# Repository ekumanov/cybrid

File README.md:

# Cybrid

**A DIY hybrid piano: a real grand piano action turned into a MIDI controller.**

Instruments with a real wooden piano action and a digital sound engine are called *hybrid* pianos;
the Yamaha AvantGrand N1X I own is one. I wondered whether I could build something similar myself,
and in 2020 finished **Cybrid**: one optical sensor above each hammer of a grand piano action
measures the hammer's speed just before it hits the stop rail, and a Teensy turns that into MIDI.
The name was suggested on a piano forum: **Cyb**erGene (my nickname) + hy**brid**.

I'm a Java engineer and had no experience with electronics, PCB design, microcontrollers or piano
regulation when I started, so I learned it all along the way. V1 is the result: it works and I
play it daily, but many decisions are clumsy. This repository documents it as built, and is
structured so that better versions can follow.

▶ **Demo video:**

## How it works, in short

- A **CNY70** reflective optical sensor above each hammer shank gives a voltage that rises as the
  hammer approaches.
- Three **LM339** comparators per key turn it into three digital signals: the hammer is past the
  damper point, the escapement point, or the strike point. Trimpots set the three points.
- A **Teensy** scans all 88 keys in a few microseconds through a shared bus, times the flight from
  escapement to strike, and sends MIDI note-on with a velocity derived from it.

Full explanation: [How it works](docs/v1/how-it-works.md).

<table>
<tr>
<td align="center"><br><b>Sensor board</b> × 88</td>
<td align="center"><br><b>Note board</b> × 18 (5 keys each)</td>
<td align="center"><br><b>Teensy board</b> × 1</td>
</tr>
</table>

## Versions

| Version | Status | |
|---|---|---|
| **V1** | Built 2019–2020, played daily. Comparators + trimpots, Teensy 3.6/4.1, hand-made ribbon cable. | [hardware](hardware/v1) · [firmware](firmware/v1) · [docs](docs/v1) |

## Documentation

| | |
|---|---|
| [How it works](docs/v1/how-it-works.md) | Sensing principle, grouping and multiplexing, scanning algorithm, velocity |
| [Hardware](hardware/v1/README.md) | The three boards: schematics, 3D renders, bill of materials, manufacturing files |
| [Build guide](docs/v1/build-guide.md) | Soldering, mounting, wiring, power, the ribbon cable, known problems |
| [Firmware](firmware/v1/README.md) | Building and flashing (Arduino IDE or PlatformIO), configuration, tests |
| [Calibration](docs/v1/calibration.md) | Setting the three points of every key |
| [Photo gallery](docs/v1/gallery.md) | The V1 build in pictures |
| [Changelog](CHANGELOG.md) | |

## Repository layout

```
cybrid/
├── hardware/v1/      KiCad 10 projects for the three boards, export script for fab outputs
├── firmware/v1/      Teensy firmware (PlatformIO project), calibration sketches, host tests
├── docs/
│   ├── v1/           how it works, build guide, calibration, gallery
│   └── images/v1/    photos and board renders
├── LICENSES/         full license texts
└── .github/          CI: firmware build + tests, hardware export
```

Each future version gets its own `hardware/vN`, `firmware/vN` and `docs/vN`, so V1 stays buildable
as it is.

## Community

Discussion thread on the
[PianoClack forum](https://pianoclack.com/forum/d/107-cybrid-a-diy-midi-controller-with-grand-piano-action).
I'm glad Cybrid has inspired other projects, several of them better designed and easier to
reproduce. Questions, issues and pull requests are welcome.

## Credits

Using voltage comparators to turn the analog sensor signal into fast digital signals was
suggested by **Marcos Daniel** on the PianoWorld forums. Everything else (multiplexing, PCB design,
firmware and the integration with the grand piano action) is by Evgeni Kumanov (CyberGene).

## License

Open source hardware and software. Hardware is under
[CERN-OHL-P-2.0](LICENSES/CERN-OHL-P-2.0.txt), software under [MIT](LICENSES/MIT.txt), and
documentation and photos under [CC-BY-4.0](LICENSES/CC-BY-4.0.txt). See [LICENSE](LICENSE) for
details.

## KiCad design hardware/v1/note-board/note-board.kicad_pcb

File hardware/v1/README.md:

# Cybrid V1 hardware

KiCad sources for the three V1 boards, as fabricated and built in 2019–2020. How they work together is
explained in [How it works](../../docs/v1/how-it-works.md); assembly is in the
[build guide](../../docs/v1/build-guide.md).

| | Sensor board | Note board | Teensy board |
|---|---|---|---|
| 3D render |  |  |  |
| As built |  |  |  |
| Role | 1 CNY70 above one hammer shank | 5 keys: comparators, trimpots, bus transceivers | Teensy, ribbon-cable socket, power distribution |
| Qty for 88 keys | 88 | 18 | 1 |
| Size | 24.1 × 8.9 mm | 53.3 × 76.2 mm | 57.1 × 87.6 mm |
| Layers | 2 | 2 | 2 |
| Schematic | [PDF](sensor-board/sensor-board-schematic.pdf) | [PDF](note-board/note-board-schematic.pdf) | [PDF](teensy-board/teensy-board-schematic.pdf) |
| KiCad project | [`sensor-board/`](sensor-board) | [`note-board/`](note-board) | [`teensy-board/`](teensy-board) |

Top and bottom renders of every board are in [`docs/images/v1/boards`](../../docs/images/v1/boards).
The 3D renders show no Teensy and no USB-B socket, because KiCad's library has no 3D models for them.

## Opening the designs

Install [KiCad](https://www.kicad.org/download/) **10 or newer** and open a board's `.kicad_pro`
file. No extra libraries are needed: the schematic symbols and footprints are embedded in the
design files, and the 3D models come from KiCad's standard library.

```
hardware/v1/
├── export.sh                 regenerates all outputs (see below)
├── tools/                    one-off scripts used to modernise the 2020 files (kept for reference)
├── sensor-board/
│   ├── sensor-board.kicad_pro    project
│   ├── sensor-board.kicad_sch    schematic
│   ├── sensor-board.kicad_pcb    board
│   └── sensor-board-schematic.pdf
├── note-board/   (same layout)
└── teensy-board/ (same layout)
```

## Manufacturing

Generate the fabrication files with:

```bash
hardware/v1/export.sh
```

This writes `hardware/v1/build/<board>/` (not committed): Gerbers and Excellon drill files in
`fab/` and zipped as `<board>-fab.zip` (upload that to any PCB fab), the schematic PDF, the BOM as
CSV, 3D renders, and ERC/DRC reports. `DOCS=1 hardware/v1/export.sh` also refreshes the schematic
PDFs and renders committed for the docs. GitHub Actions runs the same export on every change to
`hardware/` and keeps the outputs as a downloadable artifact.

My boards were made as standard 2-layer, 1.6 mm FR-4 boards with **white solder mask and black
silkscreen**. All SMD parts are 0603 or SOIC, hand-solderable.

## Bill of materials

Per board, from the schematics (`<board>-bom.csv` from the export has the reference designators).
The links are where I bought parts in 2020 (a Bulgarian distributor); any equivalent part works.

### Note board (× 18 for 88 keys)

| Qty | Part | Value / type | Package | Refs |
|---|---|---|---|---|
| 4 | Quad voltage comparator | LM339AD (TI) | SOIC-14 | CMP1–CMP4 |
| 2 | Octal bus transceiver, 3-state | SN74LVC245ADWR (TI) | SOIC-20 wide (7.5 mm) | TX1, TX2 |
| 15 | Trimpot, multi-turn, top adjust | 10 kΩ (20 kΩ also works), Bourns 3296W | THT | RV11–RV53 |
| 17 | Resistor | 10 kΩ | 0603 | R1, R11–R44 |
| 5 | Resistor (sensor load) | 4.7 kΩ | 0603 | R18, R28, R38, R48, R58 |
| 6 | Capacitor, ceramic (back side) | 100 nF | 0603 | C1–C6 |
| 1 | Box header, straight | 2×17, 2.54 mm (IDC-34) | THT | COMM1 |
| 2 | Pin header + 1 jumper | 2×9, 2.54 mm | THT | SEL1, SEL2 |
| 5 | Pin header (back side, sensor cables) | 1×3, 2.54 mm | THT | J1–J5 |
| 2 | Wire-to-board header, power in/out | JST XH 3-pin (B3B-XH-A) | THT | PWR1, PWR2 |

### Sensor board (× 88)

| Qty | Part | Value / type | Package | Refs |
|---|---|---|---|---|
| 1 | Reflective optical sensor | Vishay CNY70 | THT | S1 |
| 1 | Resistor (LED current, ~16 mA) | 240 Ω | 0603 | R1 |
| 1 | Pin header, right angle, male (cut from a longer strip) | 1×3, 2.54 mm | THT | J1 |

### Teensy board (× 1)

| Qty | Part | Value / type | Package | Refs |
|---|---|---|---|---|
| 1 | Microcontroller | Teensy 4.1 (or 3.6), with pin headers | module | CTL1 |
| 1 | Box header, straight | 2×17, 2.54 mm (IDC-34) | THT | COMM1 |
| 4 | Wire-to-board header, power out | JST XH 3-pin (B3B-XH-A) | THT | PWR1–PWR4 |
| 1 | USB-B socket (power input only) | | THT | USB1 |
| 1 | DC barrel jack (alternative power input) | | THT | J11 |
| 1 | Pin header + jumper (3.3 V from Teensy, not recommended) | 1×2, 2.54 mm | THT | JP1 |
| 3 | Resistor, pedal current limit | **not fitted** | 0603 | R1–R3 |
| 1 | 3.3 V linear regulator, on a small perfboard (not on the PCB) | any, low current | | |

### Cabling and mechanics

| Qty (88 keys) | Part |
|---|---|
| 88 | 3-wire female–female Dupont cable, 10 cm (sensor to note board) |
| 19 | IDC-34 ribbon connector (18 note boards + Teensy board) |
| ~1.5 m | 34-wire ribbon cable, 1.27 mm pitch |
| 2 per board | JST XH 3-pin housings + crimp contacts, and solid-core wire for the power chain |
| 1 | 5 V power supply, ≥ 2 A (USB charger) |
| 1 | Aluminium profile for the sensor rail, threaded rods and nuts to fix it to the action |

### Totals for 88 keys

| Part | Qty |
|---|---|
| CNY70 | 88 |
| LM339AD | 72 |
| SN74LVC245ADWR | 36 |
| Trimpot 10 kΩ, Bourns 3296W | 270 (264 used) |
| Resistor 0603: 10 kΩ / 4.7 kΩ / 240 Ω | 306 / 90 / 88 |
| Capacitor 0603 100 nF | 108 |

## What changed in 2026

The boards were drawn in KiCad 5.0 in 2019–2020. In 2026 the projects were migrated to KiCad 10
without changing the design:

- Converted to the KiCad 10 file format; files renamed (`My Piano Controller Note Module 3 (5-note,
  5V pots)` became `note-board`). The old rescue/cache libraries are no longer needed because KiCad
  now embeds symbols in the schematic.
- **Connectivity verified unchanged:** for every board, each net in the schematic connects exactly
  the same pads as on the board (49, 73 and 4 nets), and DRC reports no unconnected items.
- Component values written into the schematics (they were generic `R`, `C`, `R_POT_TRIM` and
  existed only in e-mails). The unfitted R1–R3 on the Teensy board are marked *do not populate*.
- 3D models assigned from KiCad's library (most footprints had none), and the board stackup records
  the real colours (white mask, black silk), so 3D views look like the real boards.
  ([`tools/`](tools) has the scripts used.)
- Copper zones refilled with KiCad 10's filler; pours may differ slightly from the 2020 Gerbers.
- Generated files (Gerbers, drill files, netlists, `.bak` files, the Freerouting `.dsn`/`.ses`
  files) were removed from the repository. The 2020 versions remain in the git history.

### Known warnings

ERC and DRC report warnings that predate the migration or are cosmetic:

- *Net name mismatches between schematic and board* (`+3V3` vs `+3.3V`, auto-generated net names):
  KiCad 10 names nets differently from KiCad 5; the connections are identical (see above).
  Don't run **Update PCB from Schematic** without reviewing the changes: it would also try to swap
  the custom Teensy footprint.
- *Library links*: the footprints and symbols came from KiCad 5 libraries and custom downloads
  that no longer exist under those names. The embedded copies are complete.
- Silkscreen text size, overlapping courtyards and silk-to-edge clearances: fabricated and working
  as is.

### About the autorouting

The note and Teensy boards were routed with [Freerouting](https://github.com/freerouting/freerouting), the
open-source Java autorouter (exported from KiCad as `.dsn`, routed, imported back as `.ses`). The
result lives in the `.kicad_pcb` now, so neither the tool nor the intermediate files are needed to
open, change or manufacture the boards. For a future version, Freerouting is available as a KiCad
plugin from the Plugin and Content Manager. For dense or timing-sensitive boards, hand-routing
the critical nets is still the better choice.

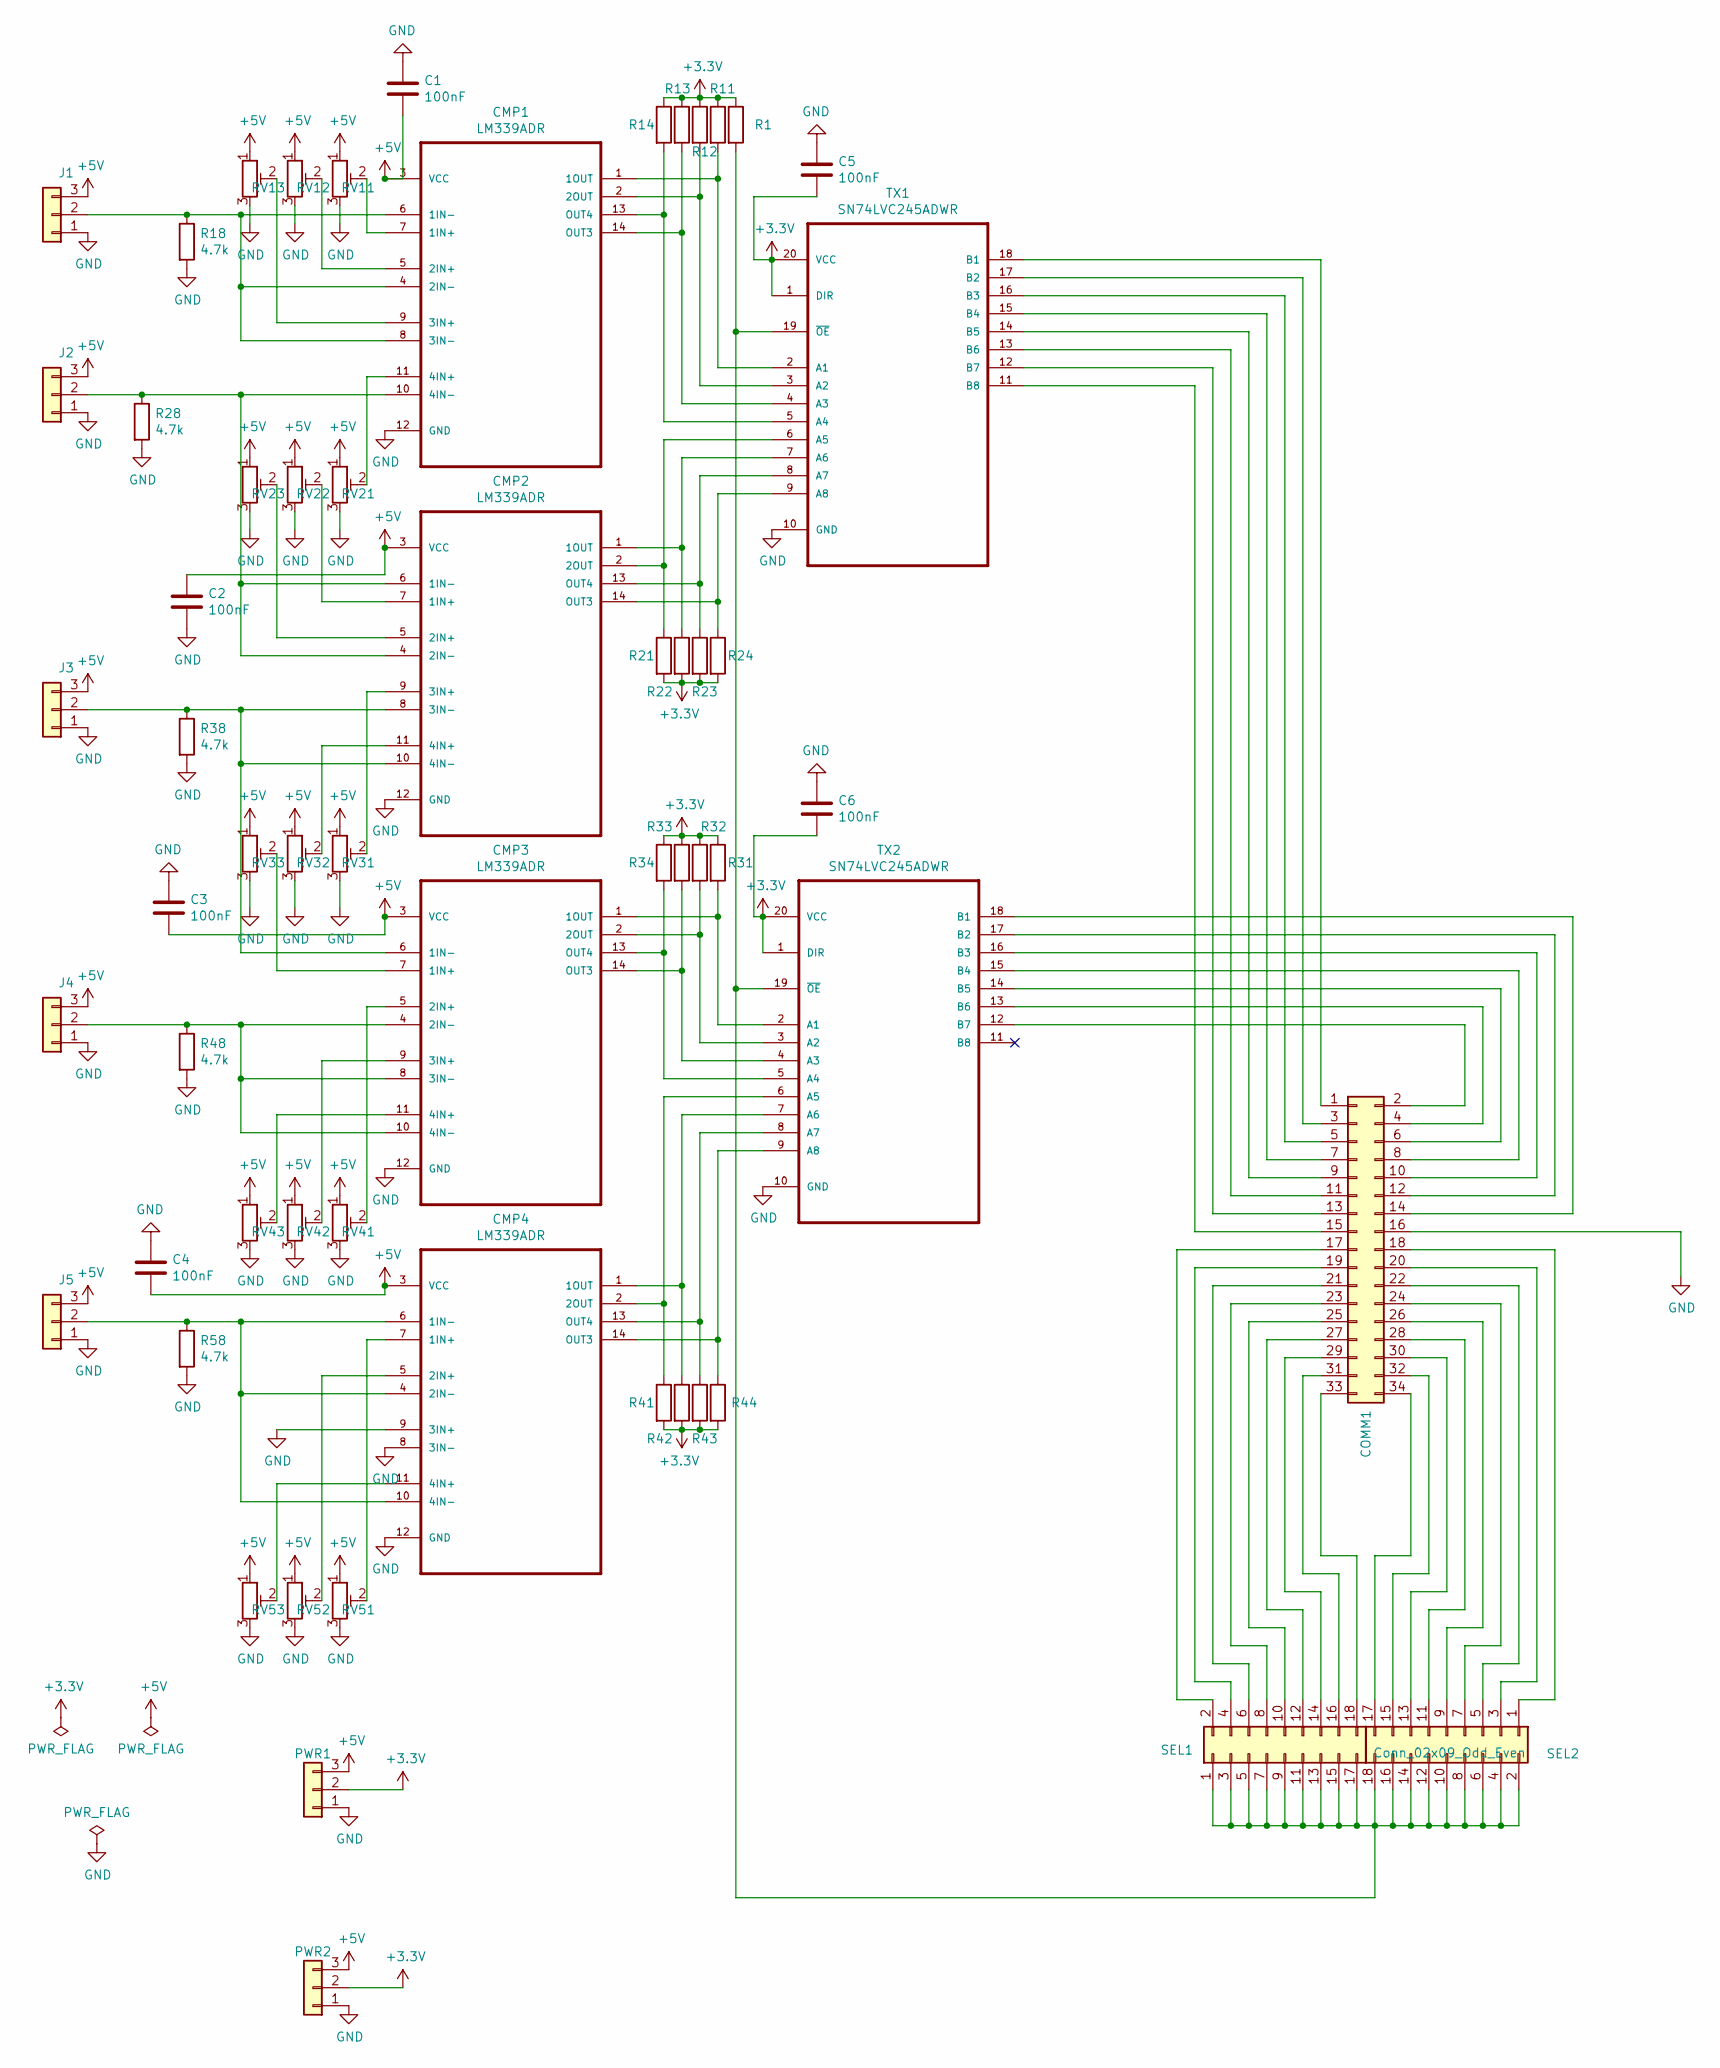
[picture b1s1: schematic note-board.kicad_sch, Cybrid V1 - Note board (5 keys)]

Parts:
C1, C2, C3, C4, C5, C6: 100nF; C_0603_HandSoldering
CMP1, CMP2, CMP3, CMP4: LM339ADR; SOIC127P600X175-14N
COMM1: Conn_02x17_Odd_Even; Multicomp_MC9A12-3434_2x17x2.54mm_Straight
J1, J2, J3, J4, J5: Conn_01x03; Pin_Header_Straight_1x03_Pitch2.54mm
PWR1, PWR2: Conn_01x03; JST_XH_B03B-XH-A_03x2.50mm_Straight
R1, R11, R12, R13, R14, R21, R22, R23, R24, R31, R32, R33, R34, R41, R42, R43, R44: 10k; R_0603_HandSoldering
R18, R28, R38, R48, R58: 4.7k; R_0603_HandSoldering
RV11, RV12, RV13, RV21, RV22, RV23, RV31, RV32, RV33, RV41, RV42, RV43, RV51, RV52, RV53: 10k; Potentiometer_Trimmer_Bourns_3296W
SEL1, SEL2: Conn_02x09_Odd_Even; Pin_Header_Straight_2x09_Pitch2.54mm
TX1, TX2: SN74LVC245ADWR; SOIC127P1030X265-20N

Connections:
+3V3: C5.2, C6.2, PWR1.2, PWR2.2, R1.1, R11.1, R12.1, R13.1, R14.1, R21.2, R22.2, R23.2, R24.2, R31.1, R32.1, R33.1, R34.1, R41.2, R42.2, R43.2, R44.2, TX1.1 (DIR), TX1.20 (VCC), TX2.1 (DIR), TX2.20 (VCC)
+5V: C1.2, C2.1, C3.2, C4.2, CMP1.3 (VCC), CMP2.3 (VCC), CMP3.3 (VCC), CMP4.3 (VCC), J1.3, J2.3, J3.3, J4.3, J5.3, PWR1.3, PWR2.3, RV11.1, RV12.1, RV13.1, RV21.1, RV22.1, RV23.1, RV31.1, RV32.1, RV33.1, RV41.1, RV42.1, RV43.1, RV51.1, RV52.1, RV53.1
GND: C1.1, C2.2, C3.1, C4.1, C5.1, C6.1, CMP1.12 (GND), CMP2.12 (GND), CMP3.12 (GND), CMP4.8 (3IN-), CMP4.9 (3IN+), CMP4.12 (GND), COMM1.16, J1.1, J2.1, J3.1, J4.1, J5.1, PWR1.1, PWR2.1, R18.2, R28.2, R38.2, R48.2, R58.2, RV11.3, RV12.3, RV13.3, RV21.3, RV22.3, RV23.3, RV31.3, RV32.3, RV33.3, RV41.3, RV42.3, RV43.3, RV51.3, RV52.3, RV53.3, TX1.10 (GND), TX2.10 (GND)
unnamed: CMP1.1 (1OUT), R11.2, TX1.2 (A1)
unnamed: CMP1.2 (2OUT), R12.2, TX1.3 (A2)
unnamed: CMP1.4 (2IN-), CMP1.6 (1IN-), CMP1.8 (3IN-), J1.2, R18.1
unnamed: CMP1.5 (2IN+), RV12.2
unnamed: CMP1.7 (1IN+), RV11.2
unnamed: CMP1.9 (3IN+), RV13.2
unnamed: CMP1.10 (4IN-), CMP2.4 (2IN-), CMP2.6 (1IN-), J2.2, R28.1
unnamed: CMP1.11 (4IN+), RV21.2
unnamed: CMP1.13 (OUT4), R14.2, TX1.5 (A4)
unnamed: CMP1.14 (OUT3), R13.2, TX1.4 (A3)
unnamed: CMP2.1 (1OUT), R22.1, TX1.7 (A6)
unnamed: CMP2.2 (2OUT), R21.1, TX1.6 (A5)
unnamed: CMP2.5 (2IN+), RV23.2
unnamed: CMP2.7 (1IN+), RV22.2
unnamed: CMP2.9 (3IN+), RV31.2
unnamed: CMP2.8 (3IN-), CMP2.10 (4IN-), CMP3.6 (1IN-), J3.2, R38.1
unnamed: CMP2.11 (4IN+), RV32.2
unnamed: CMP2.13 (OUT4), R23.1, TX1.8 (A7)
unnamed: CMP2.14 (OUT3), R24.1, TX1.9 (A8)
unnamed: CMP3.1 (1OUT), R31.2, TX2.2 (A1)
unnamed: CMP3.2 (2OUT), R32.2, TX2.3 (A2)
unnamed: CMP3.5 (2IN+), RV41.2
unnamed: CMP3.7 (1IN+), RV33.2
unnamed: CMP3.9 (3IN+), RV42.2
unnamed: CMP3.4 (2IN-), CMP3.8 (3IN-), CMP3.10 (4IN-), J4.2, R48.1
unnamed: CMP3.11 (4IN+), RV43.2
unnamed: CMP3.13 (OUT4), R34.2, TX2.5 (A4)
unnamed: CMP3.14 (OUT3), R33.2, TX2.4 (A3)
unnamed: CMP4.1 (1OUT), R42.1, TX2.7 (A6)
unnamed: CMP4.2 (2OUT), R41.1, TX2.6 (A5)
unnamed: CMP4.5 (2IN+), RV52.2
unnamed: CMP4.7 (1IN+), RV51.2
unnamed: CMP4.4 (2IN-), CMP4.6 (1IN-), CMP4.10 (4IN-), J5.2, R58.1
unnamed: CMP4.11 (4IN+), RV53.2
unnamed: CMP4.13 (OUT4), R43.1, TX2.8 (A7)
unnamed: CMP4.14 (OUT3), R44.1, TX2.9 (A8)
unnamed: COMM1.1, TX1.18 (B1)
unnamed: COMM1.2, TX2.12 (B7)
unnamed: COMM1.3, TX1.17 (B2)
unnamed: COMM1.4, TX2.13 (B6)
unnamed: COMM1.5, TX1.16 (B3)
unnamed: COMM1.6, TX2.14 (B5)
unnamed: COMM1.7, TX1.15 (B4)
unnamed: COMM1.8, TX2.15 (B4)
unnamed: COMM1.9, TX1.14 (B5)
unnamed: COMM1.10, TX2.16 (B3)
unnamed: COMM1.11, TX1.13 (B6)
unnamed: COMM1.12, TX2.17 (B2)
unnamed: COMM1.13, TX1.12 (B7)
unnamed: COMM1.14, TX2.18 (B1)
unnamed: COMM1.15, TX1.11 (B8)
unnamed: COMM1.17, SEL1.2
unnamed: COMM1.18, SEL2.1
unnamed: COMM1.19, SEL1.4
unnamed: COMM1.20, SEL2.3
unnamed: COMM1.21, SEL1.6
unnamed: COMM1.22, SEL2.5
unnamed: COMM1.23, SEL1.8
unnamed: COMM1.24, SEL2.7
unnamed: COMM1.25, SEL1.10
unnamed: COMM1.26, SEL2.9
unnamed: COMM1.27, SEL1.12
unnamed: COMM1.28, SEL2.11
unnamed: COMM1.29, SEL1.14
unnamed: COMM1.30, SEL2.13
unnamed: COMM1.31, SEL1.16
unnamed: COMM1.32, SEL2.15
unnamed: COMM1.33, SEL1.18
unnamed: COMM1.34, SEL2.17
unnamed: R1.2, SEL1.1, SEL1.3, SEL1.5, SEL1.7, SEL1.9, SEL1.11, SEL1.13, SEL1.15, SEL1.17, SEL2.2, SEL2.4, SEL2.6, SEL2.8, SEL2.10, SEL2.12, SEL2.14, SEL2.16, SEL2.18, TX1.19 (~OE), TX2.19 (~OE)

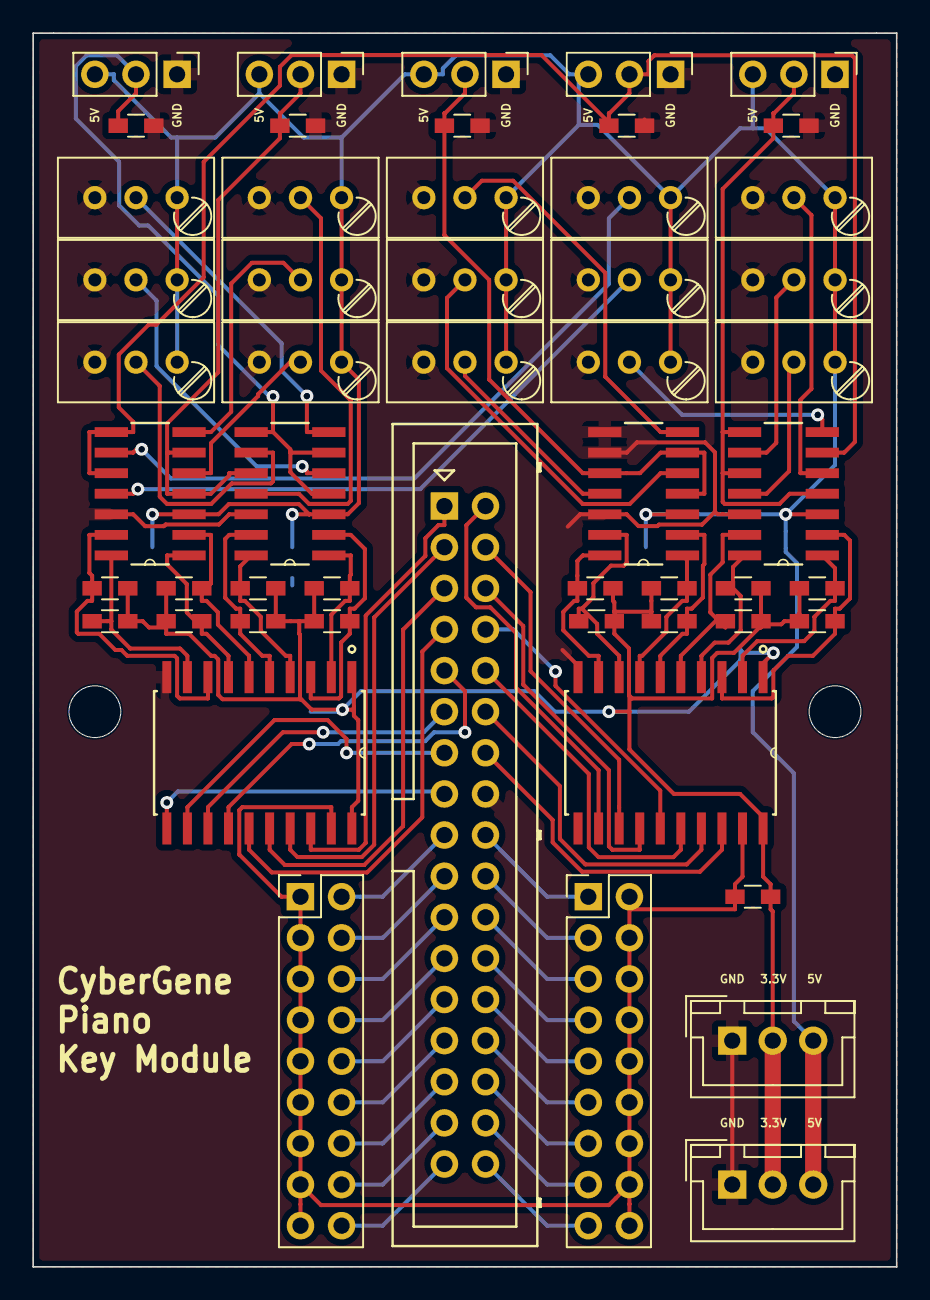
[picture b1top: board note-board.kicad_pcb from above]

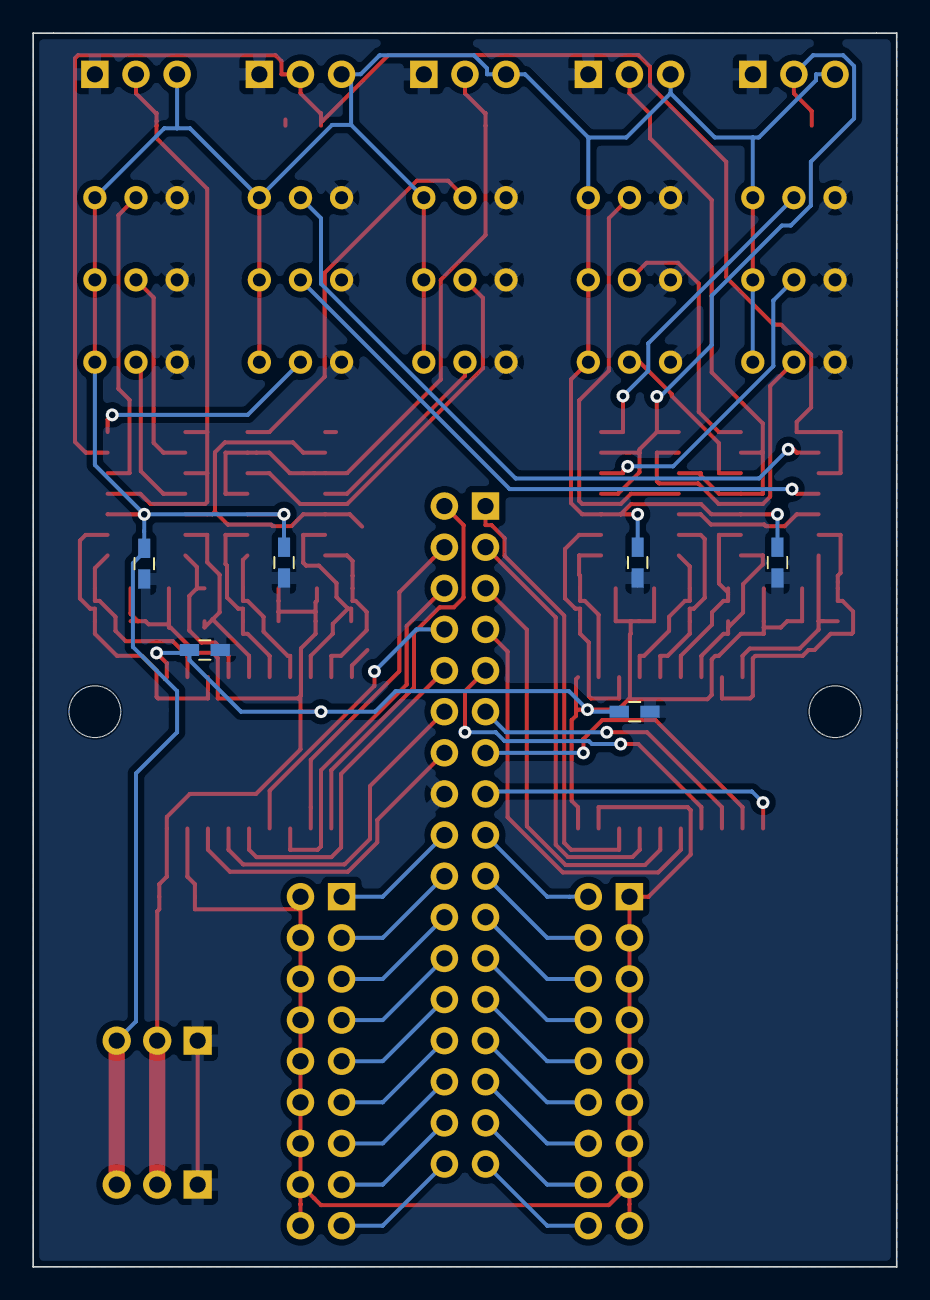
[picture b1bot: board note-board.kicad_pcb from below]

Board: 2 copper layers, 53.3 x 76.2 mm, 61 parts (6 on the bottom side), 73 nets.

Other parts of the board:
HOLE1, HOLE2: MountingHole_3.2mm_M3

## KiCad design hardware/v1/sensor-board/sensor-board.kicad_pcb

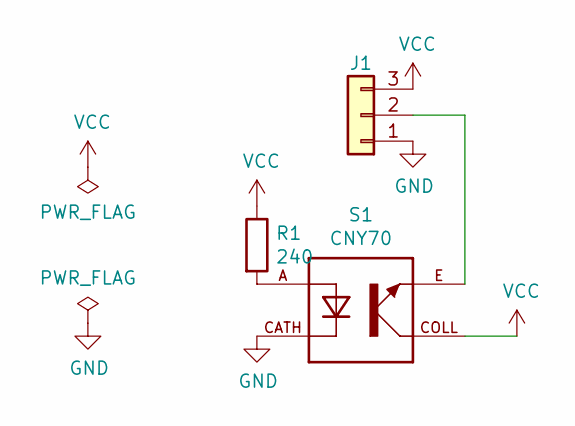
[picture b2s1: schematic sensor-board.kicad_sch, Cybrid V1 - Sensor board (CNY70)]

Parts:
J1: Conn_01x03; Socket_Strip_Straight_1x03_Pitch2.54mm
R1: 240; R_0603_HandSoldering
S1: CNY70; DIPS254W50P254L710H600Q4

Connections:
GND: J1.1, S1.CATH
unnamed: J1.2, S1.E
unnamed: R1.2, S1.A
VCC: J1.3, R1.1, S1.COLL

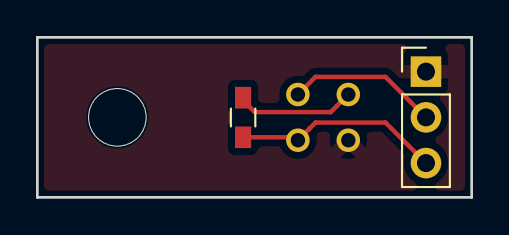
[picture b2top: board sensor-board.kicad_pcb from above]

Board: 2 copper layers, 24.1 x 8.9 mm, 3 parts (1 on the bottom side), 4 nets.

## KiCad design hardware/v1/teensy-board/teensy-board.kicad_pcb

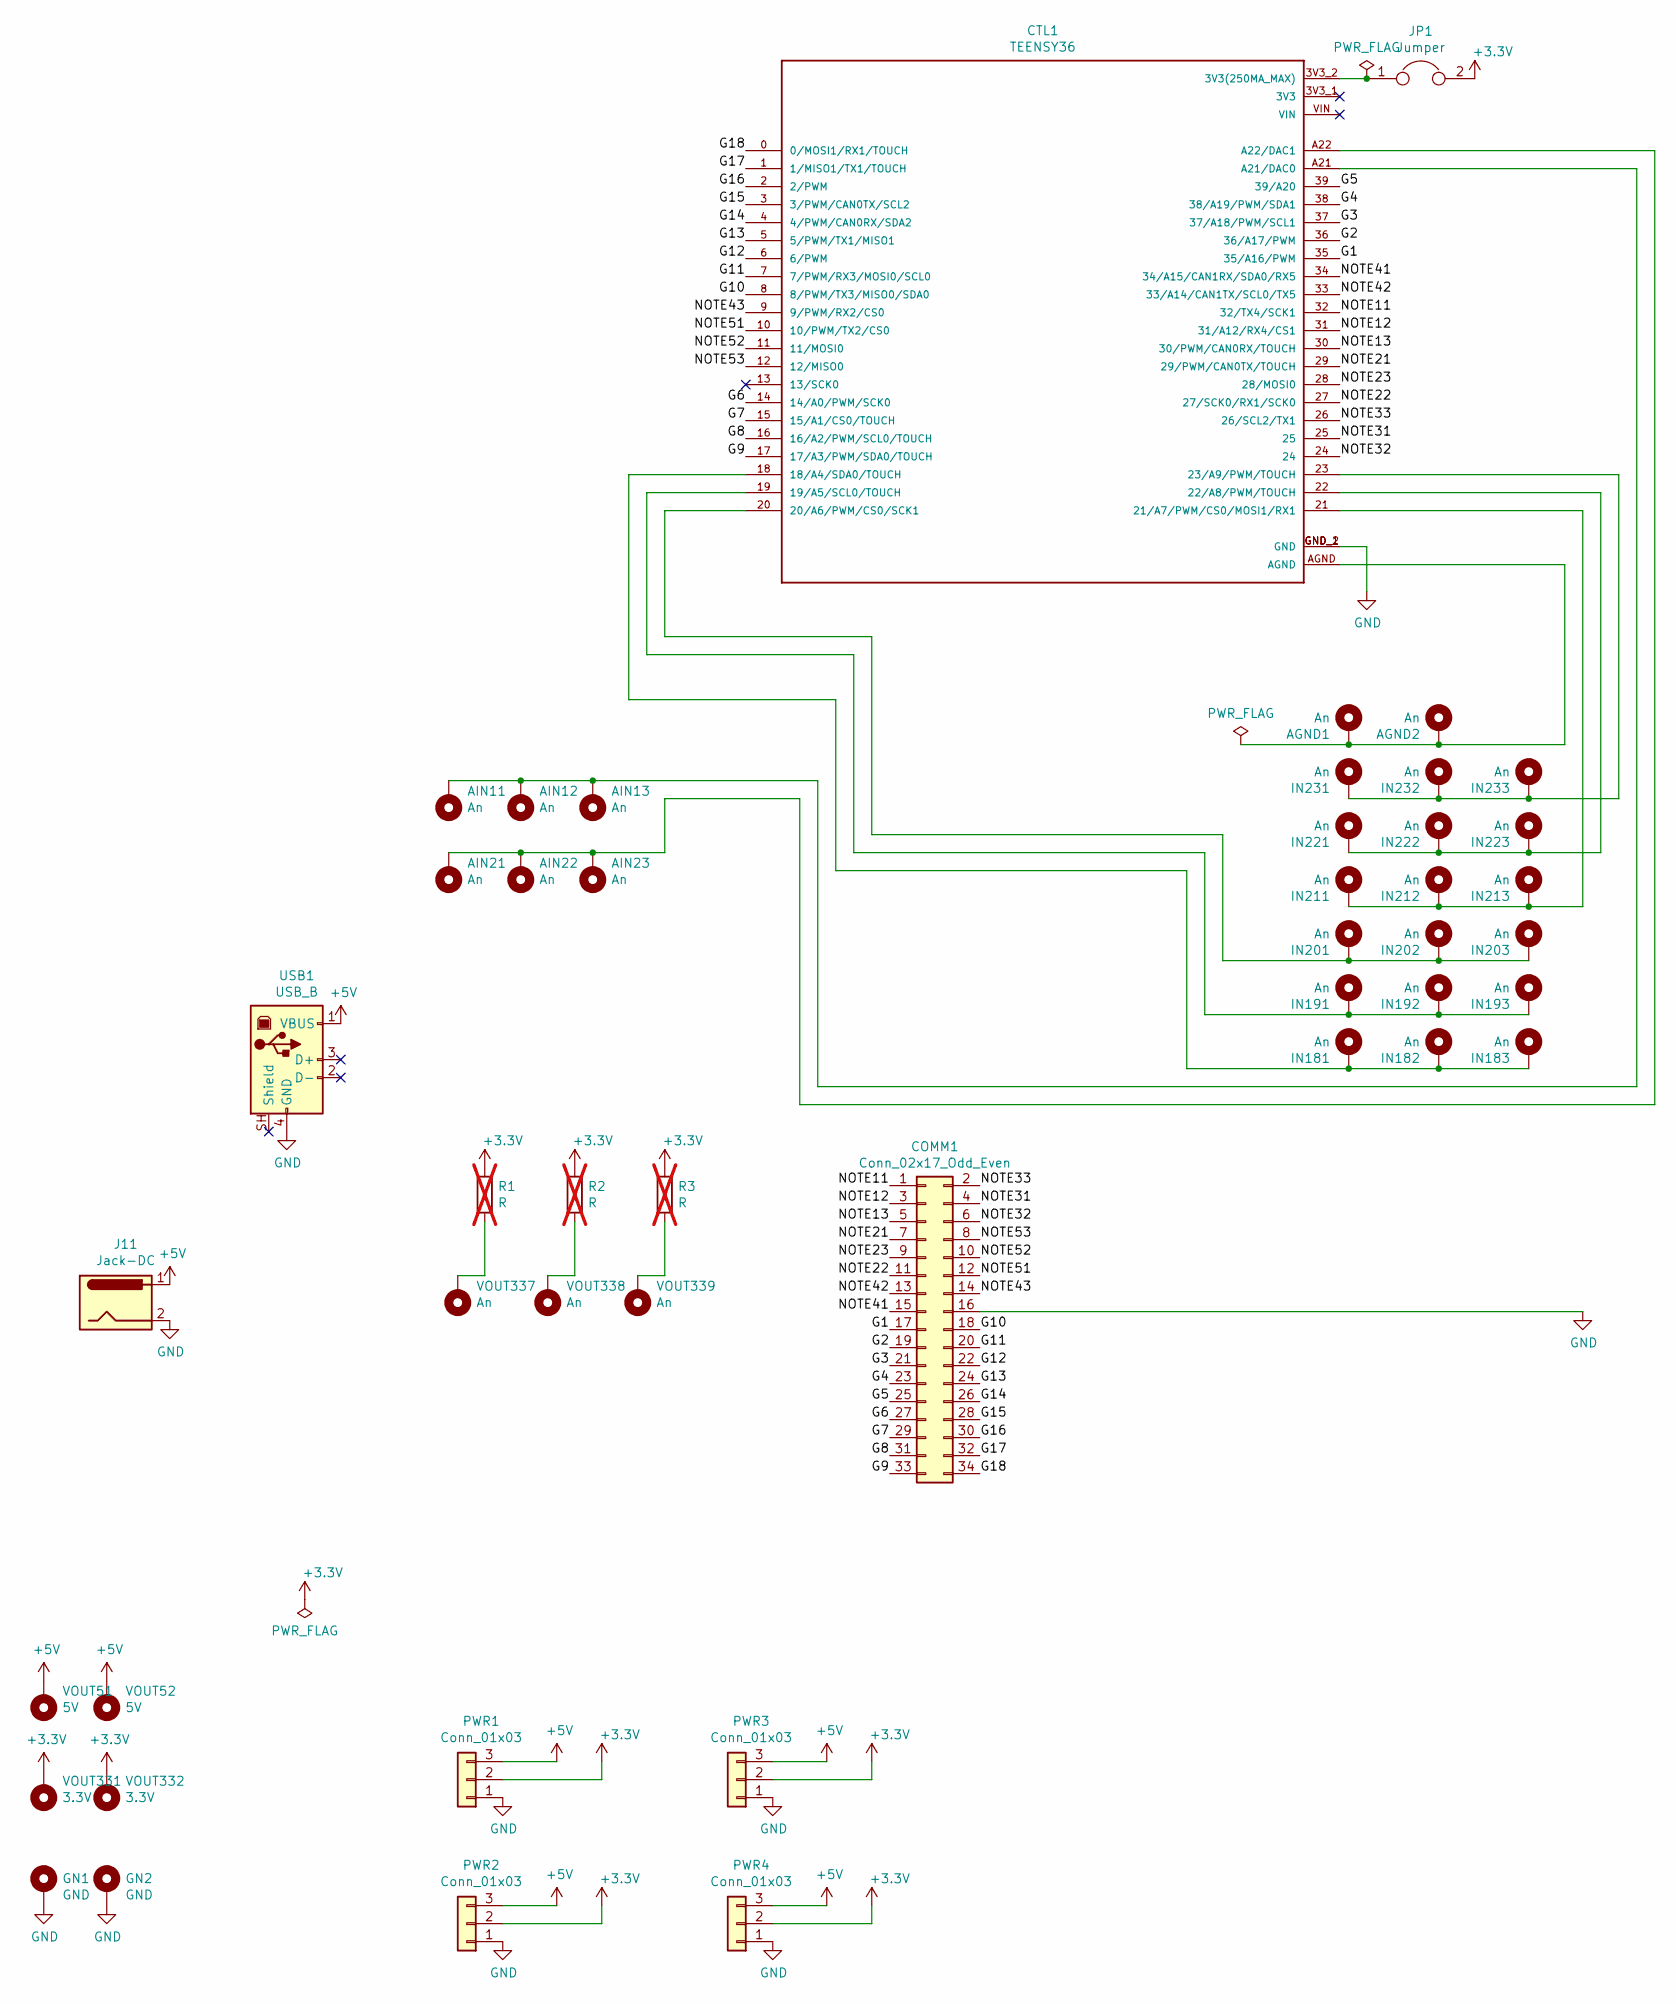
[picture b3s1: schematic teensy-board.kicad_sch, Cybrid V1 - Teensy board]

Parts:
AGND1, AGND2: An; SolderWirePad_single_0-8mmDrill
AIN11, AIN12, AIN13, AIN21, AIN22, AIN23: An; SolderWirePad_single_0-8mmDrill
COMM1: Conn_02x17_Odd_Even; Multicomp_MC9A12-3434_2x17x2.54mm_Straight
CTL1: TEENSY36; SPARKFUN_TEENSY36
GN1, GN2: GND; SolderWirePad_single_1mmDrill
IN181, IN182, IN183, IN191, IN192, IN193, IN201, IN202, IN203, IN211, IN212, IN213, IN221, IN222, IN223, IN231, IN232, IN233: An; SolderWirePad_single_0-8mmDrill
J11: Jack-DC; BARREL_JACK
JP1: Jumper; Pin_Header_Straight_1x02_Pitch2.54mm
PWR1, PWR2, PWR3, PWR4: Conn_01x03; JST_XH_B03B-XH-A_03x2.50mm_Straight
R1, R2, R3: R; R_0603_HandSoldering; not fitted
USB1: USB_B
VOUT51, VOUT52: 5V; SolderWirePad_single_1mmDrill
VOUT331, VOUT332: 3.3V; SolderWirePad_single_1mmDrill
VOUT337, VOUT338, VOUT339: An; SolderWirePad_single_0-8mmDrill

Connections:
+3V3: JP1.2, PWR1.2, PWR2.2, PWR3.2, PWR4.2, R1.1, R2.1, R3.1, VOUT331.1, VOUT332.1
+5V: J11.1, PWR1.3, PWR2.3, PWR3.3, PWR4.3, USB1.1 (VBUS), VOUT51.1, VOUT52.1
/G1: COMM1.17, CTL1.35 (35/A16/PWM)
/G2: COMM1.19, CTL1.36 (36/A17/PWM)
/G3: COMM1.21, CTL1.37 (37/A18/PWM/SCL1)
/G4: COMM1.23, CTL1.38 (38/A19/PWM/SDA1)
/G5: COMM1.25, CTL1.39 (39/A20)
/G6: COMM1.27, CTL1.14 (14/A0/PWM/SCK0)
/G7: COMM1.29, CTL1.15 (15/A1/CS0/TOUCH)
/G8: COMM1.31, CTL1.16 (16/A2/PWM/SCL0/TOUCH)
/G9: COMM1.33, CTL1.17 (17/A3/PWM/SDA0/TOUCH)
/G10: COMM1.18, CTL1.8 (8/PWM/TX3/MISO0/SDA0)
/G11: COMM1.20, CTL1.7 (7/PWM/RX3/MOSI0/SCL0)
/G12: COMM1.22, CTL1.6 (6/PWM)
/G13: COMM1.24, CTL1.5 (5/PWM/TX1/MISO1)
/G14: COMM1.26, CTL1.4 (4/PWM/CAN0RX/SDA2)
/G15: COMM1.28, CTL1.3 (3/PWM/CAN0TX/SCL2)
/G16: COMM1.30, CTL1.2 (2/PWM)
/G17: COMM1.32, CTL1.1 (1/MISO1/TX1/TOUCH)
/G18: COMM1.34, CTL1.0 (0/MOSI1/RX1/TOUCH)
/NOTE11: COMM1.1, CTL1.32 (32/TX4/SCK1)
/NOTE12: COMM1.3, CTL1.31 (31/A12/RX4/CS1)
/NOTE13: COMM1.5, CTL1.30 (30/PWM/CAN0RX/TOUCH)
/NOTE21: COMM1.7, CTL1.29 (29/PWM/CAN0TX/TOUCH)
/NOTE22: COMM1.11, CTL1.27 (27/SCK0/RX1/SCK0)
/NOTE23: COMM1.9, CTL1.28 (28/MOSI0)
/NOTE31: COMM1.4, CTL1.25
/NOTE32: COMM1.6, CTL1.24
/NOTE33: COMM1.2, CTL1.26 (26/SCL2/TX1)
/NOTE41: COMM1.15, CTL1.34 (34/A15/CAN1RX/SDA0/RX5)
/NOTE42: COMM1.13, CTL1.33 (33/A14/CAN1TX/SCL0/TX5)
/NOTE43: COMM1.14, CTL1.9 (9/PWM/RX2/CS0)
/NOTE51: COMM1.12, CTL1.10 (10/PWM/TX2/CS0)
/NOTE52: COMM1.10, CTL1.11 (11/MOSI0)
/NOTE53: COMM1.8, CTL1.12 (12/MISO0)
GND: COMM1.16, CTL1.GND_1 (GND), CTL1.GND_2 (GND), GN1.1, GN2.1, J11.2, PWR1.1, PWR2.1, PWR3.1, PWR4.1, USB1.4 (GND)
unnamed: AGND1.1, AGND2.1, CTL1.AGND
unnamed: AIN11.1, AIN12.1, AIN13.1, CTL1.A21 (A21/DAC0)
unnamed: AIN21.1, AIN22.1, AIN23.1, CTL1.A22 (A22/DAC1)
unnamed: CTL1.3V3_2 (3V3(250MA_MAX)), JP1.1
unnamed: CTL1.18 (18/A4/SDA0/TOUCH), IN181.1, IN182.1, IN183.1
unnamed: CTL1.19 (19/A5/SCL0/TOUCH), IN191.1, IN192.1, IN193.1
unnamed: CTL1.20 (20/A6/PWM/CS0/SCK1), IN201.1, IN202.1, IN203.1
unnamed: CTL1.21 (21/A7/PWM/CS0/MOSI1/RX1), IN211.1, IN212.1, IN213.1
unnamed: CTL1.22 (22/A8/PWM/TOUCH), IN221.1, IN222.1, IN223.1
unnamed: CTL1.23 (23/A9/PWM/TOUCH), IN231.1, IN232.1, IN233.1
unnamed: R1.2, VOUT337.1
unnamed: R2.2, VOUT338.1
unnamed: R3.2, VOUT339.1

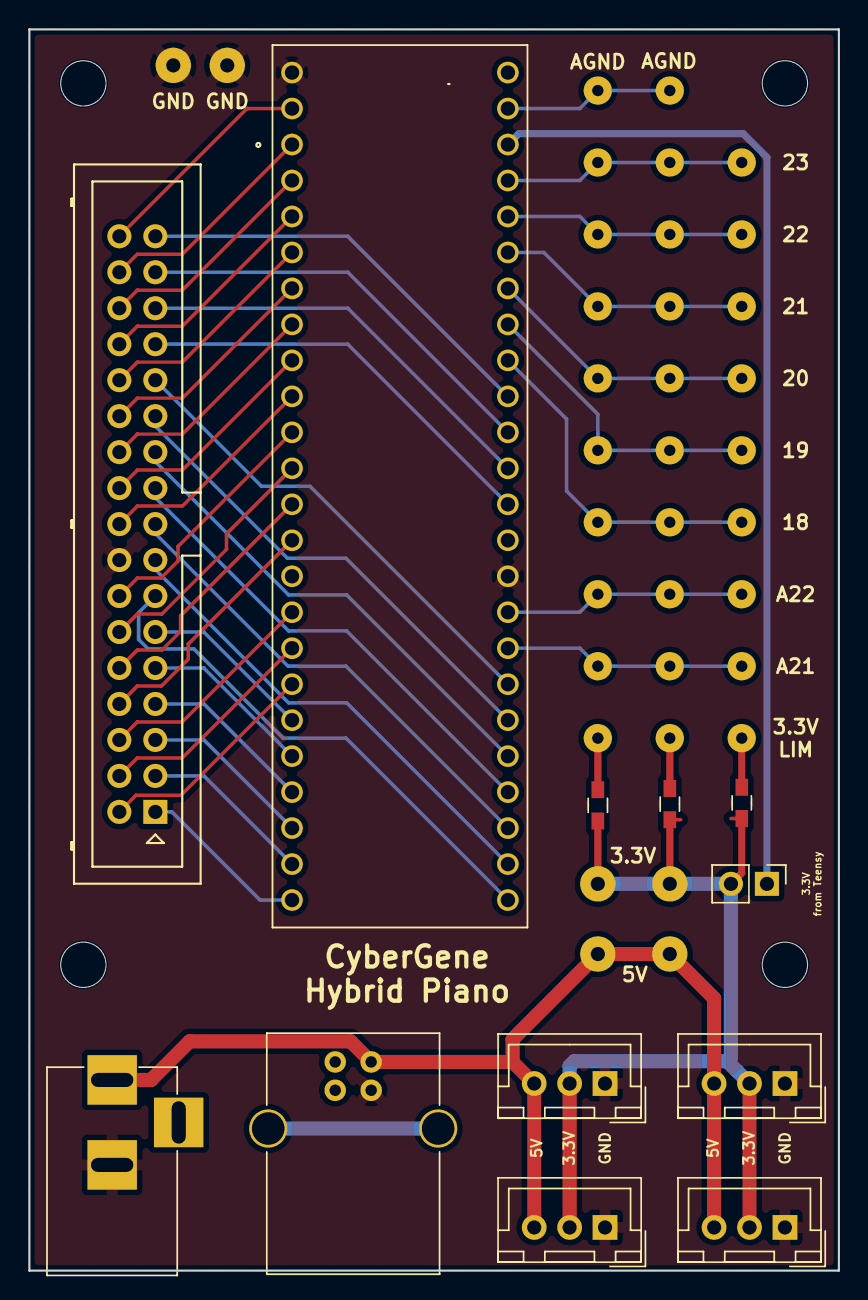
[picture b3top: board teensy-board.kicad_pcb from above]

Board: 2 copper layers, 57.1 x 87.6 mm, 51 parts (0 on the bottom side), 49 nets.

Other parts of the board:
HOLE1, HOLE2, HOLE3, HOLE4: MountingHole_3.2mm_M3

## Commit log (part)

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2020-04-26 .gitignore
2020-04-29 Introduction and the basic principle of the voltage comparator and the optical sensor.
2020-04-29 Rewording and velocity measurement
2020-04-29 paragraph
2020-05-01 typo
2020-07-06 The main teensy program code. It contains some customizations, for instance a fix for my faulty IDC cable, calibrations for my Kawai half-pedal, hammer action group weight coefficients, etc. but let 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
2020-07-06 The calibration programs for the three sensors. Based on old and ugly code but work for what they are meant to do.
2020-07-06 PCB designs (created in KiCad)
2020-07-06 A lot of information, images and stuff put in a hurry. Nopt well organized and probably full of typos.
2020-07-28 Adapt for Teensy 4.1 (A21 analog input pin is now A16), add more quasi-NOOPs
2020-12-28 Link to Jay Kominek's great project
2021-07-13 Added some excerpts from email communication regarding exact parts, etc.
2021-07-13 formatting
2021-10-17 Add a link to the PianoClack Forum
2021-10-18 Grammar fixes
2021-10-18 Reflow the text to fit 120 characters
2025-04-29 Reword README.md
2025-04-29 The complete set of files, since I had forgotten some files on my initial commit
2026-01-04 Used Gemini and Claude AI to analyze my code and apply various optimizations, as well as document the code. This is not tested, however it's based on a few hours of back and forth with the AI assista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
2026-01-04 Switch inputs to INPUT_PULLUP, refine comments

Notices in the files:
README.md:
License: CERN-OHL-P | MIT | CC-BY-4.0
